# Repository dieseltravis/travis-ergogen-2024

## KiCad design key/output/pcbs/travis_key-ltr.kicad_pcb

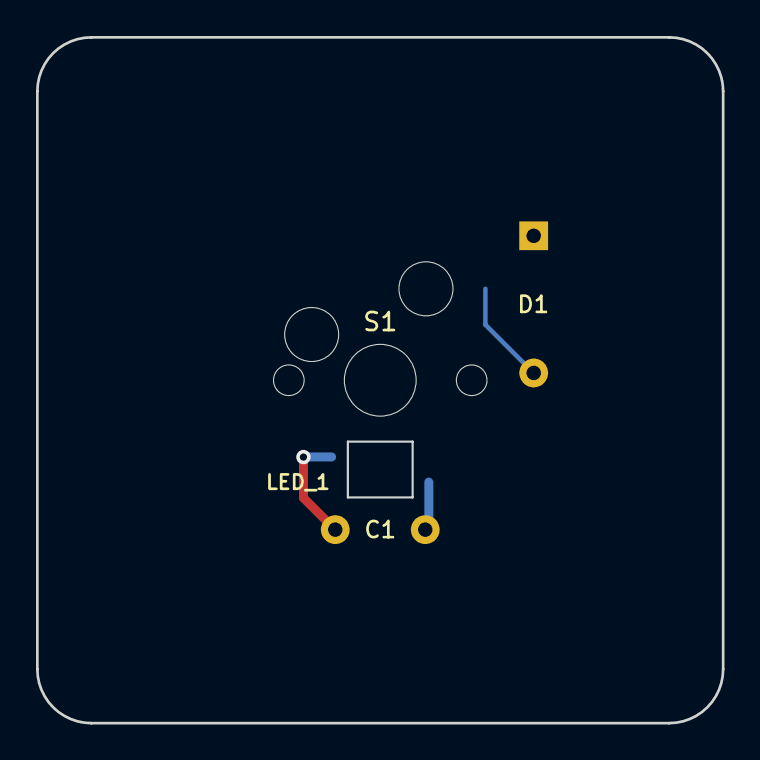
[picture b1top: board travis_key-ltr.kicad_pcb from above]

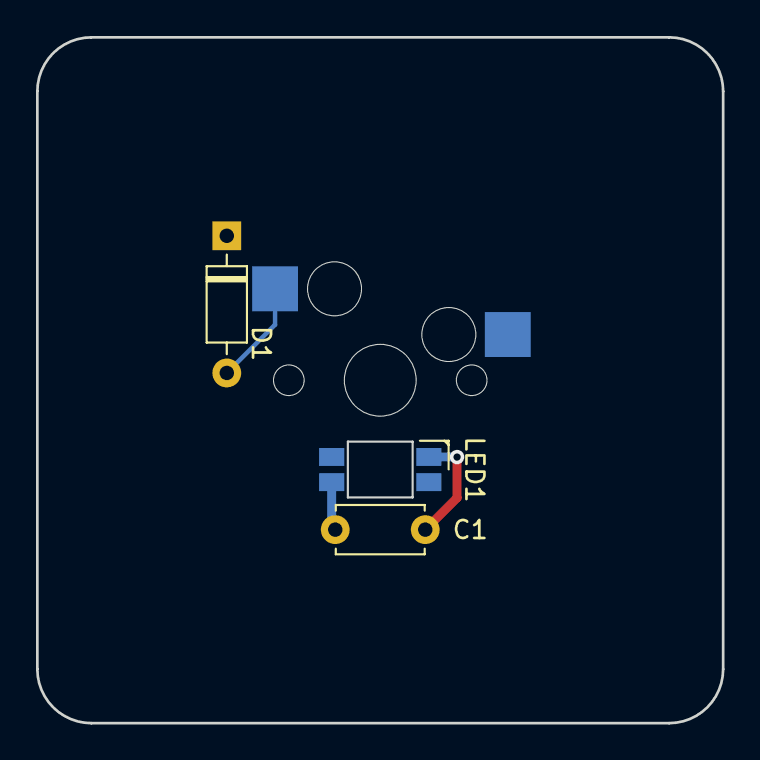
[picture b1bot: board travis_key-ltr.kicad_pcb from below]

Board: 2 copper layers, 38.1 x 38.1 mm, 4 parts (3 on the bottom side), 3 nets.

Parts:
C1: 104; C_Disc_D4.7mm_W2.5mm_P5.00mm
D1: 1N4148; Diode_DO-35
LED1: SK6812mini-e; led_SK6812mini-e (per-key single-side)
S1: MX

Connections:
GND: C1.2, LED1.3
RAW: C1.1, LED1.1
single_A_one: D1.2, S1.2

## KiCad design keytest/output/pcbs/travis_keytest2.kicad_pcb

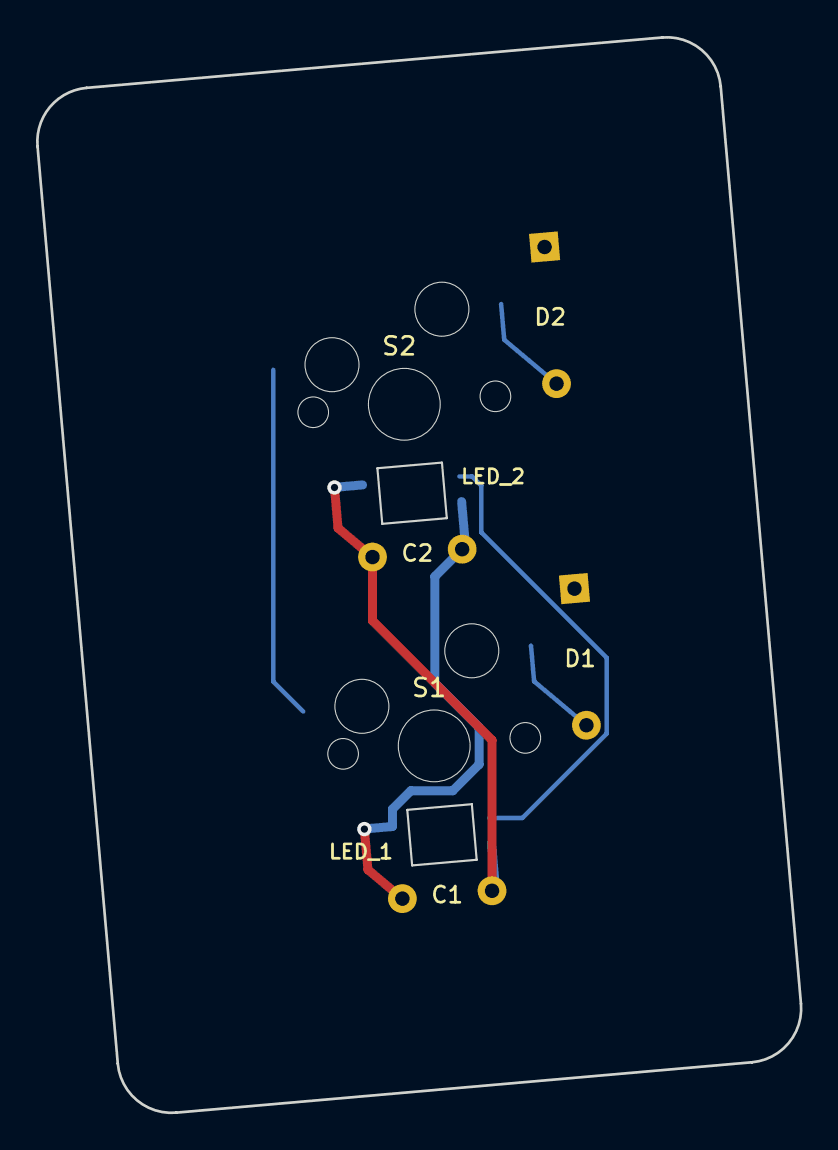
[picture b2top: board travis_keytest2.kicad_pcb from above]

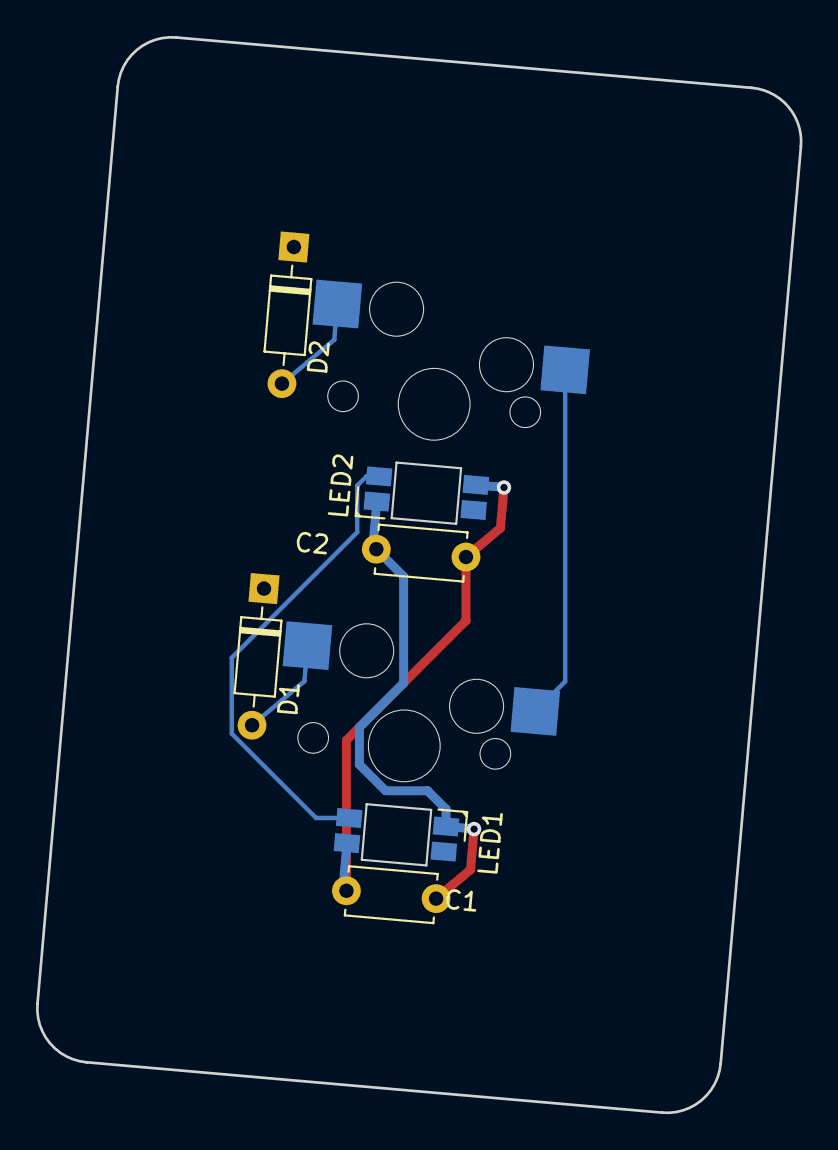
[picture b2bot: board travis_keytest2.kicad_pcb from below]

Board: 2 copper layers, 42.4 x 59.7 mm, 8 parts (6 on the bottom side), 6 nets.

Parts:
C1, C2: 104; C_Disc_D4.7mm_W2.5mm_P5.00mm
D1, D2: 1N4148; Diode_DO-35
LED1, LED2: SK6812mini-e; led_SK6812mini-e (per-key single-side)
S1, S2: Kailh MX Switch Sockets; MX

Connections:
GND: C1.2, C2.2, LED1.3, LED2.3
LED_2: LED1.2, LED2.4
RAW: C1.1, C2.1, LED1.1, LED2.1
col0: S1.1, S2.1
single_A_one: D1.2, S1.2
single_A_two: D2.2, S2.2

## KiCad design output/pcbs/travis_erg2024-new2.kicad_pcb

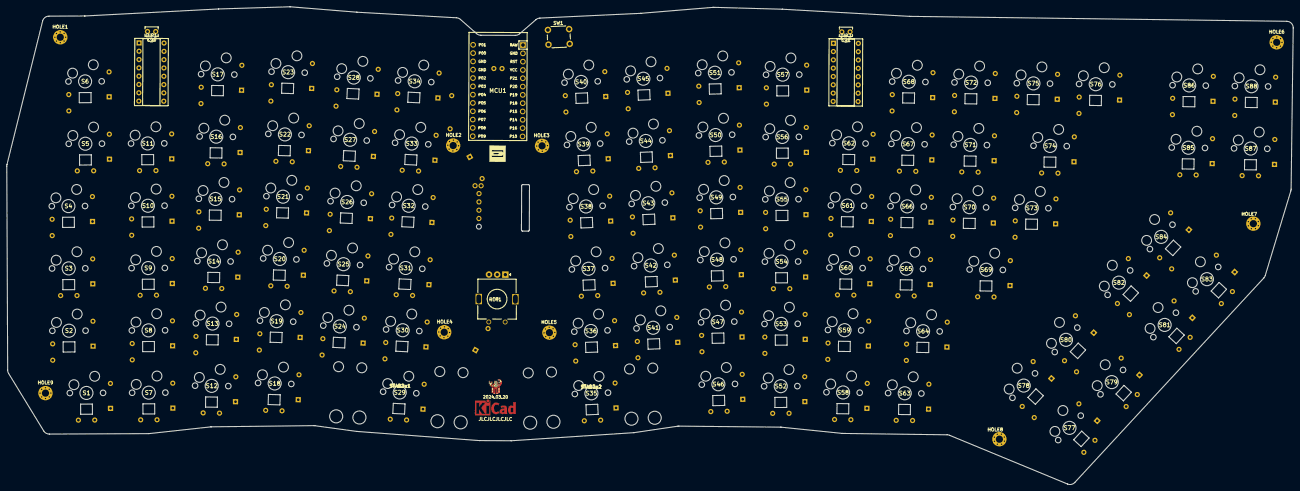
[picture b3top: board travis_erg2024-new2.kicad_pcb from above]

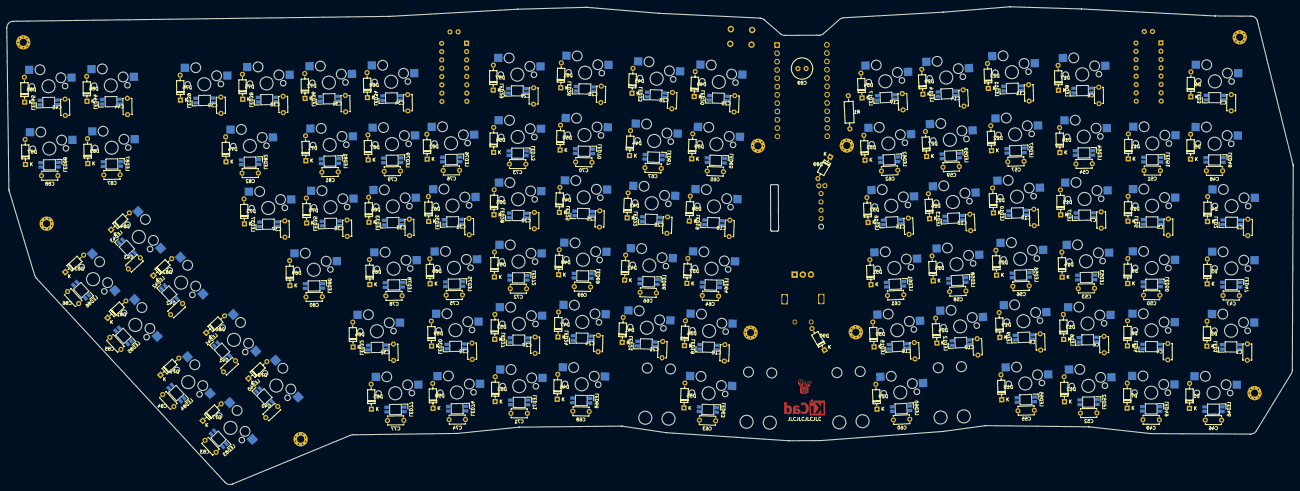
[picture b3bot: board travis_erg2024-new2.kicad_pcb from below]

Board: 2 copper layers, 393.3 x 146.1 mm, 379 parts (268 on the bottom side), 210 nets, no tracks yet.

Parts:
C1, C2, C3, C4, C5, C6, C7, C8, C9, C10, C11, C12, C13, C14, C15, C16, C17, C18, C19, C20, C21, C22, C23, C24, C25, C26, C27, C28, C29, C30, C31, C32, C33, C34, C35, C36, C37, C38, C39, C40, C41, C42, C43, C44, C45, C46, C47, C48, C49, C50, C51, C52, C53, C54, C55, C56, C57, C58, C59, C60, C61, C62, C63, C64, C65, C66, C67, C68, C69, C70, C71, C72, C73, C74, C75, C76, C77, C78, C79, C80, C81, C82, C83, C84, C85, C86, C87, C88: C_Disc_D4.7mm_W2.5mm_P5.00mm
C89: C_Radial_D6.3mm_H11.0mm_P2.50mm
C90, C91: C_Disc_D3.8mm_W2.6mm_P2.50mm
D1, D2, D3, D4, D5, D6, D7, D8, D9, D10, D11, D12, D13, D14, D15, D16, D17, D18, D19, D20, D21, D22, D23, D24, D25, D26, D27, D28, D29, D30, D31, D32, D33, D34, D35, D36, D37, D38, D39, D40, D41, D42, D43, D44, D45, D46, D47, D48, D49, D50, D51, D52, D53, D54, D55, D56, D57, D58, D59, D60, D61, D62, D63, D64, D65, D66, D67, D68, D69, D70, D71, D72, D73, D74, D75, D76, D77, D78, D79, D80, D81, D82, D83, D84, D85, D86, D87, D88, D89, D90: 1N4148; Diode_DO-35
DIP1, DIP2: DIP-16_W7.62mm_Socket
HOLE1, HOLE2, HOLE3, HOLE4, HOLE5, HOLE6, HOLE7, HOLE8, HOLE9: MountingHole_2.2mm_M2_Pad_Via
LED1, LED2, LED3, LED4, LED5, LED6, LED7, LED8, LED9, LED10, LED11, LED12, LED13, LED14, LED15, LED16, LED17, LED18, LED19, LED20, LED21, LED22, LED23, LED24, LED25, LED26, LED27, LED28, LED29, LED30, LED31, LED32, LED33, LED34, LED35, LED36, LED37, LED38, LED39, LED40, LED41, LED42, LED43, LED44, LED45, LED46, LED47, LED48, LED49, LED50, LED51, LED52, LED53, LED54, LED55, LED56, LED57, LED58, LED59, LED60, LED61, LED62, LED63, LED64, LED65, LED66, LED67, LED68, LED69, LED70, LED71, LED72, LED73, LED74, LED75, LED76, LED77, LED78, LED79, LED80, LED81, LED82, LED83, LED84, LED85, LED86, LED87, LED88: led_SK6812mini-e (per-keysingle-side)
LOGO1: ergogen
LOGO2: travis
MCU1: ProMicro
R1: R_Axial_DIN0207_L6.3mm_D2.5mm_P10.16mm_Horizontal
ROT1: rotary_encoder
S1, S2, S3, S4, S5, S6, S7, S8, S9, S10, S11, S12, S13, S14, S15, S16, S17, S18, S19, S20, S21, S22, S23, S24, S25, S26, S27, S28, S29, S30, S31, S32, S33, S34, S35, S36, S37, S38, S39, S40, S41, S42, S43, S44, S45, S46, S47, S48, S49, S50, S51, S52, S53, S54, S55, S56, S57, S58, S59, S60, S61, S62, S63, S64, S65, S66, S67, S68, S69, S70, S71, S72, S73, S74, S75, S76, S77, S78, S79, S80, S81, S82, S83, S84, S85, S86, S87, S88: MX
STAB2u1, STAB2u2: Stabilizer_MX_2.00u
STAB3u1, STAB3u2: Stabilizer_MX_3.00u
SW1: SW_PUSH_6mm_H4.3mm
SYM1: KiCad-Logo_5mm_Copper

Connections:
GND: C1.2, C2.2, C3.2, C4.2, C5.2, C6.2, C7.2, C8.2, C9.2, C10.2, C11.2, C12.2, C13.2, C14.2, C15.2, C16.2, C17.2, C18.2, C19.2, C20.2, C21.2, C22.2, C23.2, C24.2, C25.2, C26.2, C27.2, C28.2, C29.2, C30.2, C31.2, C32.2, C33.2, C34.2, C35.2, C36.2, C37.2, C38.2, C39.2, C40.2, C41.2, C42.2, C43.2, C44.2, C45.2, C46.2, C47.2, C48.2, C49.2, C50.2, C51.2, C52.2, C53.2, C54.2, C55.2, C56.2, C57.2, C58.2, C59.2, C60.2, C61.2, C62.2, C63.2, C64.2, C65.2, C66.2, C67.2, C68.2, C69.2, C70.2, C71.2, C72.2, C73.2, C74.2, C75.2, C76.2, C77.2, C78.2, C79.2, C80.2, C81.2, C82.2, C83.2, C84.2, C85.2, C86.2, C87.2, C88.2, C89.2, C90.2, C91.2, DIP1.4, DIP1.8, DIP2.4, DIP2.5, DIP2.8, LED1.3, LED2.3, LED3.3, LED4.3, LED5.3, LED6.3, LED7.3, LED8.3, LED9.3, LED10.3, LED11.3, LED12.3, LED13.3, LED14.3, LED15.3, LED16.3, LED17.3, LED18.3, LED19.3, LED20.3, LED21.3, LED22.3, LED23.3, LED24.3, LED25.3, LED26.3, LED27.3, LED28.3, LED29.3, LED30.3, LED31.3, LED32.3, LED33.3, LED34.3, LED35.3, LED36.3, LED37.3, LED38.3, LED39.3, LED40.3, LED41.3, LED42.3, LED43.3, LED44.3, LED45.3, LED46.3, LED47.3, LED48.3, LED49.3, LED50.3, LED51.3, LED52.3, LED53.3, LED54.3, LED55.3, LED56.3, LED57.3, LED58.3, LED59.3, LED60.3, LED61.3, LED62.3, LED63.3, LED64.3, LED65.3, LED66.3, LED67.3, LED68.3, LED69.3, LED70.3, LED71.3, LED72.3, LED73.3, LED74.3, LED75.3, LED76.3, LED77.3, LED78.3, LED79.3, LED80.3, LED81.3, LED82.3, LED83.3, LED84.3, LED85.3, LED86.3, LED87.3, LED88.3, MCU1.2, MCU1.15, MCU1.16, ROT1.B, SW1.1
LED: MCU1.24, R1.1
LED_0: LED17.4, R1.2
LED_1: LED14.4, LED17.2
LED_2: LED11.4, LED14.2
LED_3: LED8.4, LED11.2
LED_4: LED3.4, LED8.2
LED_5: LED3.2, LED48.4
LED_6: LED48.2, LED51.4
LED_7: LED51.2, LED54.4
LED_8: LED54.2, LED57.4
LED_9: LED57.2, LED59.4
LED_10: LED59.2, LED62.4
LED_11: LED16.4, LED62.2
LED_12: LED13.4, LED16.2
LED_13: LED10.4, LED13.2
LED_14: LED7.4, LED10.2
LED_15: LED5.4, LED7.2
LED_16: LED2.4, LED5.2
LED_17: LED2.2, LED47.4
LED_18: LED47.2, LED50.4
LED_19: LED50.2, LED53.4
LED_20: LED53.2, LED56.4
LED_21: LED56.2, LED58.4
LED_22: LED58.2, LED61.4
LED_23: LED15.4, LED61.2
LED_24: LED12.4, LED15.2
LED_25: LED9.4, LED12.2
LED_26: LED6.4, LED9.2
LED_27: LED4.4, LED6.2
LED_28: LED1.4, LED4.2
LED_29: LED1.2, LED46.4
LED_30: LED46.2, LED49.4
LED_31: LED49.2, LED52.4
LED_32: LED52.2, LED55.4
LED_33: LED55.2, LED60.4
LED_34: LED60.2, LED63.4
LED_35: LED63.2, LED68.4
LED_36: LED68.2, LED71.4
LED_37: LED71.2, LED74.4
LED_38: LED74.2, LED77.4
LED_39: LED40.4, LED77.2
LED_40: LED40.2, LED83.4
LED_41: LED83.2, LED84.4
LED_42: LED41.4, LED84.2
LED_43: LED32.4, LED41.2
LED_44: LED30.4, LED32.2
LED_45: LED27.4, LED30.2
LED_46: LED24.4, LED27.2
LED_47: LED21.4, LED24.2
LED_48: LED18.4, LED21.2
LED_49: LED18.2, LED64.4
LED_50: LED64.2, LED66.4
LED_51: LED66.2, LED69.4
LED_52: LED69.2, LED72.4
LED_53: LED72.2, LED75.4
LED_54: LED75.2, LED78.4
LED_55: LED78.2, LED80.4
LED_56: LED42.4, LED80.2
LED_57: LED42.2, LED85.4
LED_58: LED85.2, LED86.4
LED_59: LED43.4, LED86.2
LED_60: LED37.4, LED43.2
LED_61: LED35.4, LED37.2
LED_62: LED33.4, LED35.2
LED_63: LED31.4, LED33.2
LED_64: LED28.4, LED31.2
LED_65: LED25.4, LED28.2
LED_66: LED22.4, LED25.2
LED_67: LED19.4, LED22.2
LED_68: LED19.2, LED65.4
LED_69: LED65.2, LED67.4
LED_70: LED67.2, LED70.4
LED_71: LED70.2, LED73.4
LED_72: LED73.2, LED76.4
LED_73: LED76.2, LED79.4
LED_74: LED79.2, LED81.4
LED_75: LED81.2, LED82.4
LED_76: LED82.2, LED87.4
LED_77: LED87.2, LED88.4
LED_78: LED45.4, LED88.2
LED_79: LED44.4, LED45.2
LED_80: LED39.4, LED44.2
LED_81: LED38.4, LED39.2
LED_82: LED36.4, LED38.2
LED_83: LED34.4, LED36.2
LED_84: LED29.4, LED34.2
LED_85: LED26.4, LED29.2
LED_86: LED23.4, LED26.2
LED_87: LED20.4, LED23.2
RAW: C1.1, C2.1, C3.1, C4.1, C5.1, C6.1, C7.1, C8.1, C9.1, C10.1, C11.1, C12.1, C13.1, C14.1, C15.1, C16.1, C17.1, C18.1, C19.1, C20.1, C21.1, C22.1, C23.1, C24.1, C25.1, C26.1, C27.1, C28.1, C29.1, C30.1, C31.1, C32.1, C33.1, C34.1, C35.1, C36.1, C37.1, C38.1, C39.1, C40.1, C41.1, C42.1, C43.1, C44.1, C45.1, C46.1, C47.1, C48.1, C49.1, C50.1, C51.1, C52.1, C53.1, C54.1, C55.1, C56.1, C57.1, C58.1, C59.1, C60.1, C61.1, C62.1, C63.1, C64.1, C65.1, C66.1, C67.1, C68.1, C69.1, C70.1, C71.1, C72.1, C73.1, C74.1, C75.1, C76.1, C77.1, C78.1, C79.1, C80.1, C81.1, C82.1, C83.1, C84.1, C85.1, C86.1, C87.1, C88.1, C89.1, LED1.1, LED2.1, LED3.1, LED4.1, LED5.1, LED6.1, LED7.1, LED8.1, LED9.1, LED10.1, LED11.1, LED12.1, LED13.1, LED14.1, LED15.1, LED16.1, LED17.1, LED18.1, LED19.1, LED20.1, LED21.1, LED22.1, LED23.1, LED24.1, LED25.1, LED26.1, LED27.1, LED28.1, LED29.1, LED30.1, LED31.1, LED32.1, LED33.1, LED34.1, LED35.1, LED36.1, LED37.1, LED38.1, LED39.1, LED40.1, LED41.1, LED42.1, LED43.1, LED44.1, LED45.1, LED46.1, LED47.1, LED48.1, LED49.1, LED50.1, LED51.1, LED52.1, LED53.1, LED54.1, LED55.1, LED56.1, LED57.1, LED58.1, LED59.1, LED60.1, LED61.1, LED62.1, LED63.1, LED64.1, LED65.1, LED66.1, LED67.1, LED68.1, LED69.1, LED70.1, LED71.1, LED72.1, LED73.1, LED74.1, LED75.1, LED76.1, LED77.1, LED78.1, LED79.1, LED80.1, LED81.1, LED82.1, LED83.1, LED84.1, LED85.1, LED86.1, LED87.1, LED88.1, MCU1.1
RST: MCU1.3, SW1.2
VCC: C90.1, C91.1, DIP1.6, DIP1.16, DIP2.16, MCU1.4
arrows_left_bottom: D77.2, S77.2
arrows_left_top: D78.2, S78.2
arrows_right_bottom: D79.2, S79.2
arrows_right_top: D80.2, S80.2
col0: DIP1.14, S1.1, S2.1, S3.1, S4.1, S5.1, S6.1
col1: DIP1.15, S7.1, S8.1, S9.1, S10.1, S11.1
col2: MCU1.10, S12.1, S13.1, S14.1, S15.1, S16.1, S17.1
col3: MCU1.9, S18.1, S19.1, S20.1, S21.1, S22.1, S23.1
col4: MCU1.8, ROT1.1, S24.1, S25.1, S26.1, S27.1, S28.1
col5: MCU1.7, S29.1, S30.1, S31.1, S32.1, S33.1, S34.1
col6: MCU1.6, S35.1, S36.1, S37.1, S38.1, S39.1, S40.1
col7: MCU1.5, S41.1, S42.1, S43.1, S44.1, S45.1
col8: DIP2.15, S46.1, S47.1, S48.1, S49.1, S50.1, S51.1
col9: DIP2.14, S52.1, S53.1, S54.1, S55.1, S56.1, S57.1
col10: DIP2.13, S58.1, S59.1, S60.1, S61.1, S62.1
col11: DIP2.12, S63.1, S64.1, S65.1, S66.1, S67.1, S68.1
col12: DIP2.11, S69.1, S70.1, S71.1, S72.1
col13: DIP2.10, S73.1, S74.1, S75.1, S76.1
col14: DIP2.9, S78.1, S80.1, S82.1, S84.1, S85.1, S86.1
col15: DIP2.7, S77.1, S79.1, S81.1, S83.1, S87.1, S88.1
encA: MCU1.11, ROT1.A
encC: MCU1.12, ROT1.C
enc_to: D90.2, ROT1.2
matrixl_index_bottom: D24.2, S24.2
matrixl_index_func: D28.2, S28.2
matrixl_index_home: D25.2, S25.2
matrixl_index_num: D27.2, S27.2
matrixl_index_top: D26.2, S26.2
matrixl_inner_bottom: D30.2, S30.2
matrixl_inner_func: D34.2, S34.2
matrixl_inner_home: D31.2, S31.2
matrixl_inner_mod: D29.2, S29.2
matrixl_inner_num: D33.2, S33.2
matrixl_inner_top: D32.2, S32.2
matrixl_middle_bottom: D19.2, S19.2
matrixl_middle_func: D23.2, S23.2
matrixl_middle_home: D20.2, S20.2
matrixl_middle_mod: D18.2, S18.2
matrixl_middle_num: D22.2, S22.2
matrixl_middle_top: D21.2, S21.2
matrixl_outer_bottom: D2.2, S2.2
matrixl_outer_func: D6.2, S6.2
matrixl_outer_home: D3.2, S3.2
matrixl_outer_mod: D1.2, S1.2
matrixl_outer_num: D5.2, S5.2
matrixl_outer_top: D4.2, S4.2
matrixl_pinky_bottom: D8.2, S8.2
matrixl_pinky_home: D9.2, S9.2
matrixl_pinky_mod: D7.2, S7.2
matrixl_pinky_num: D11.2, S11.2
matrixl_pinky_top: D10.2, S10.2
matrixl_ring_bottom: D13.2, S13.2
matrixl_ring_func: D17.2, S17.2
matrixl_ring_home: D14.2, S14.2
matrixl_ring_mod: D12.2, S12.2
matrixl_ring_num: D16.2, S16.2
matrixl_ring_top: D15.2, S15.2
matrixr_index_bottom: D41.2, S41.2
matrixr_index_func: D45.2, S45.2
matrixr_index_home: D42.2, S42.2
matrixr_index_num: D44.2, S44.2
matrixr_index_top: D43.2, S43.2
matrixr_inner_bottom: D36.2, S36.2
matrixr_inner_func: D40.2, S40.2
matrixr_inner_home: D37.2, S37.2
matrixr_inner_mod: D35.2, S35.2
matrixr_inner_num: D39.2, S39.2
matrixr_inner_top: D38.2, S38.2
matrixr_middle_bottom: D47.2, S47.2
matrixr_middle_func: D51.2, S51.2
matrixr_middle_home: D48.2, S48.2
matrixr_middle_mod: D46.2, S46.2
matrixr_middle_num: D50.2, S50.2
matrixr_middle_top: D49.2, S49.2
matrixr_outer2_func: D72.2, S72.2
matrixr_outer2_home: D69.2, S69.2
matrixr_outer2_num: D71.2, S71.2
matrixr_outer2_top: D70.2, S70.2
matrixr_outer3_func: D75.2, S75.2
matrixr_outer3_num: D74.2, S74.2
matrixr_outer3_top: D73.2, S73.2
matrixr_outer4_func: D76.2, S76.2
matrixr_outer_bottom: D64.2, S64.2
matrixr_outer_func: D68.2, S68.2
matrixr_outer_home: D65.2, S65.2
matrixr_outer_mod: D63.2, S63.2
matrixr_outer_num: D67.2, S67.2
matrixr_outer_top: D66.2, S66.2
matrixr_pinky_bottom: D59.2, S59.2
matrixr_pinky_home: D60.2, S60.2
matrixr_pinky_mod: D58.2, S58.2
matrixr_pinky_num: D62.2, S62.2
matrixr_pinky_top: D61.2, S61.2
matrixr_ring_bottom: D53.2, S53.2
matrixr_ring_func: D57.2, S57.2
matrixr_ring_home: D54.2, S54.2
matrixr_ring_mod: D52.2, S52.2
matrixr_ring_num: D56.2, S56.2
matrixr_ring_top: D55.2, S55.2
mux0: DIP1.1, DIP2.1, MCU1.17
mux1: DIP1.2, DIP2.2, MCU1.18
mux2: DIP1.3, DIP2.3, MCU1.19
mux3: DIP1.5, DIP2.6, MCU1.20
pages_left_bottom: D81.2, S81.2
pages_left_top: D82.2, S82.2
pages_right_bottom: D83.2, S83.2
pages_right_top: D84.2, S84.2
row0: D6.1, D17.1, D23.1, D28.1, D34.1, D40.1, D45.1, D51.1, D57.1, D68.1, D72.1, D75.1, D86.1, D88.1, D89.1, DIP1.13
row1: D5.1, D11.1, D16.1, D22.1, D27.1, D33.1, D39.1, D44.1, D50.1, D56.1, D62.1, D67.1, D71.1, D74.1, D85.1, D87.1, DIP1.12
row2: D4.1, D10.1, D15.1, D21.1, D26.1, D32.1, D38.1, D43.1, D49.1, D55.1, D61.1, D66.1, D70.1, D73.1, D83.1, D84.1, DIP1.11
row3: D3.1, D9.1, D14.1, D20.1, D25.1, D31.1, D37.1, D42.1, D48.1, D54.1, D60.1, D65.1, D69.1, D76.1, D81.1, D82.1, DIP1.10
row4: D2.1, D8.1, D13.1, D19.1, D24.1, D30.1, D36.1, D41.1, D47.1, D53.1, D59.1, D64.1, D79.1, D80.1, DIP1.9
row5: D1.1, D7.1, D12.1, D18.1, D29.1, D35.1, D46.1, D52.1, D58.1, D63.1, D77.1, D78.1, D90.1, DIP1.7
special_left_bottom: D85.2, S85.2
special_left_top: D86.2, S86.2
special_right_bottom: D87.2, S87.2
special_right_top: D88.2, S88.2

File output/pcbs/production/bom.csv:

Designator,Footprint,Quantity,Value,LCSC Part #
C1,C_Radial_D6.3mm_H11.0mm_P2.50mm,1,C_Radial_D6.3mm_H11.0mm_P2.50mm,
"C2, C3",C_Disc_D3.8mm_W2.6mm_P2.50mm,2,C_Disc_D3.8mm_W2.6mm_P2.50mm,
"D1, D2, KD1, KD10, KD11, KD12, KD13, KD14, KD15, KD16, KD17, KD18, KD19, KD2, KD20, KD21, KD22, KD23, KD24, KD25, KD26, KD27, KD28, KD29, KD3, KD30, KD31, KD32, KD33, KD34, KD35, KD36, KD37, KD38, KD39, KD4, KD40, KD41, KD42, KD43, KD44, KD45, KD46, KD47, KD48, KD49, KD5, KD50, KD51, KD52, KD53, KD54, KD55, KD56, KD57, KD58, KD59, KD6, KD60, KD61, KD62, KD63, KD64, KD65, KD66, KD67, KD68, KD69, KD7, KD70, KD71, KD72, KD73, KD74, KD75, KD76, KD77, KD78, KD79, KD8, KD80, KD81, KD82, KD83, KD84, KD85, KD86, KD87, KD88, KD9",Diode_DO-35,90,1N4148,
"DIP1, DIP2",DIP-16_W7.62mm_Socket,2,DIP-16_W7.62mm_Socket,
"HOLE1, HOLE2, HOLE3, HOLE4, HOLE5, HOLE6, HOLE7, HOLE8, HOLE9",MountingHole_2.2mm_M2_Pad_Via,9,,
"KC1, KC10, KC11, KC12, KC13, KC14, KC15, KC16, KC17, KC18, KC19, KC2, KC20, KC21, KC22, KC23, KC24, KC25, KC26, KC27, KC28, KC29, KC3, KC30, KC31, KC32, KC33, KC34, KC35, KC36, KC37, KC38, KC39, KC4, KC40, KC41, KC42, KC43, KC44, KC45, KC46, KC47, KC48, KC49, KC5, KC50, KC51, KC52, KC53, KC54, KC55, KC56, KC57, KC58, KC59, KC6, KC60, KC61, KC62, KC63, KC64, KC65, KC66, KC67, KC68, KC69, KC7, KC70, KC71, KC72, KC73, KC74, KC75, KC76, KC77, KC78, KC79, KC8, KC80, KC81, KC82, KC83, KC84, KC85, KC86, KC87, KC88, KC9",C_Disc_D4.7mm_W2.5mm_P5.00mm,88,104,
"KLED1, KLED10, KLED11, KLED12, KLED13, KLED14, KLED15, KLED16, KLED17, KLED18, KLED19, KLED2, KLED20, KLED21, KLED22, KLED23, KLED24, KLED25, KLED26, KLED27, KLED28, KLED29, KLED3, KLED30, KLED31, KLED32, KLED33, KLED34, KLED35, KLED36, KLED37, KLED38, KLED39, KLED4, KLED40, KLED41, KLED42, KLED43, KLED44, KLED45, KLED46, KLED47, KLED48, KLED49, KLED5, KLED50, KLED51, KLED52, KLED53, KLED54, KLED55, KLED56, KLED57, KLED58, KLED59, KLED6, KLED60, KLED61, KLED62, KLED63, KLED64, KLED65, KLED66, KLED67, KLED68, KLED69, KLED7, KLED70, KLED71, KLED72, KLED73, KLED74, KLED75, KLED76, KLED77, KLED78, KLED79, KLED8, KLED80, KLED81, KLED82, KLED83, KLED84, KLED85, KLED86, KLED87, KLED88, KLED9",led_SK6812mini-e (per-key single-side),88,SK6812mini-e,
"KSW1, KSW10, KSW11, KSW12, KSW13, KSW14, KSW15, KSW16, KSW17, KSW18, KSW19, KSW2, KSW20, KSW21, KSW22, KSW23, KSW24, KSW25, KSW26, KSW27, KSW28, KSW29, KSW3, KSW30, KSW31, KSW32, KSW33, KSW34, KSW35, KSW36, KSW37, KSW38, KSW39, KSW4, KSW40, KSW41, KSW42, KSW43, KSW44, KSW45, KSW46, KSW47, KSW48, KSW49, KSW5, KSW50, KSW51, KSW52, KSW53, KSW54, KSW55, KSW56, KSW57, KSW58, KSW59, KSW6, KSW60, KSW61, KSW62, KSW63, KSW64, KSW65, KSW66, KSW67, KSW68, KSW69, KSW7, KSW70, KSW71, KSW72, KSW73, KSW74, KSW75, KSW76, KSW77, KSW78, KSW79, KSW8, KSW80, KSW81, KSW82, KSW83, KSW84, KSW85, KSW86, KSW87, KSW88, KSW9",MX,88,Kailh MX Switch Sockets,
MCU1,ProMicro,1,,
R1,R_Axial_DIN0207_L6.3mm_D2.5mm_P10.16mm_Horizontal,1,R_Axial_DIN0207_L6.3mm_D2.5mm_P10.16mm_Horizontal,
ROT1,rotary_encoder,1,,
SW1,SW_PUSH_6mm_H4.3mm,1,SW_PUSH_6mm_H4.3mm,

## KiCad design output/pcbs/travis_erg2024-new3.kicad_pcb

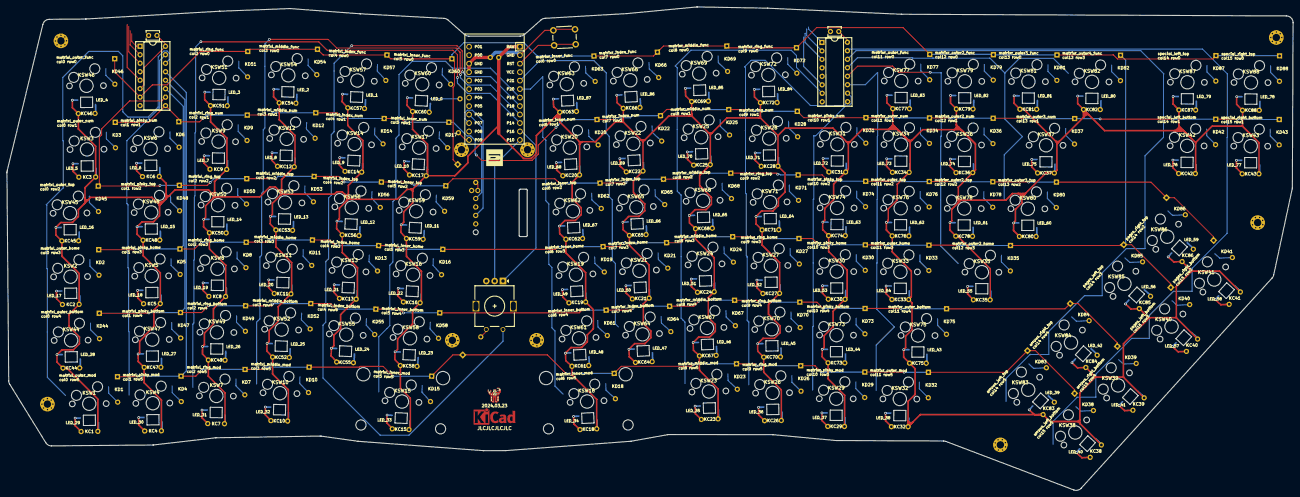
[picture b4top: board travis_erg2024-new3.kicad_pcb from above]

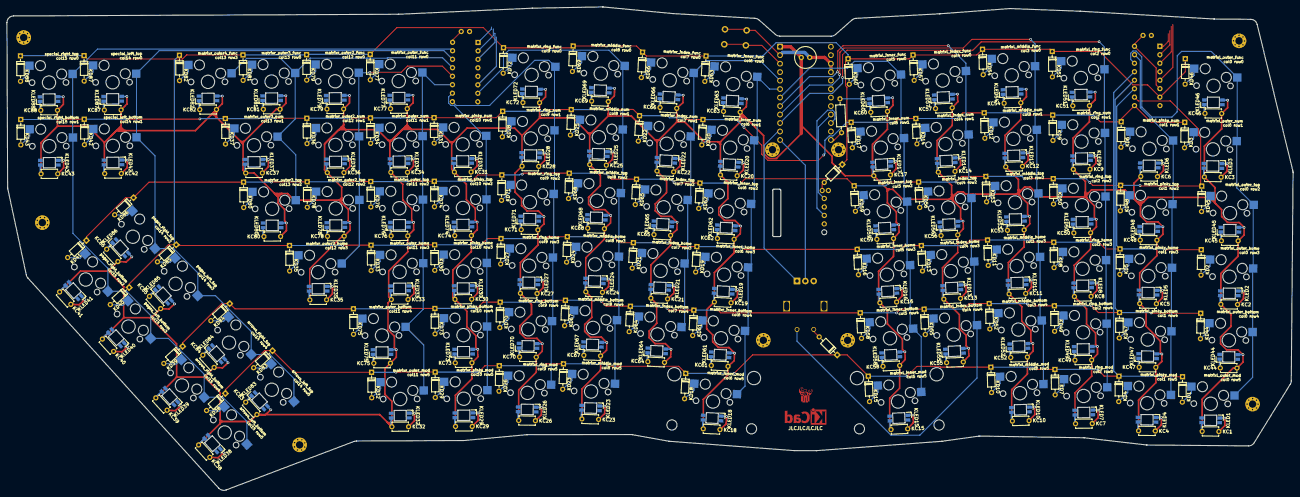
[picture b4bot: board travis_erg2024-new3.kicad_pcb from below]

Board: 2 copper layers, 385.3 x 144.8 mm, 377 parts (268 on the bottom side), 210 nets.

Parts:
C1: C_Radial_D6.3mm_H11.0mm_P2.50mm
C2, C3: C_Disc_D3.8mm_W2.6mm_P2.50mm
D1, D2: 1N4148; Diode_DO-35
DIP1, DIP2: DIP-16_W7.62mm_Socket
HOLE1, HOLE2, HOLE3, HOLE4, HOLE5, HOLE6, HOLE7, HOLE8, HOLE9: MountingHole_2.2mm_M2_Pad_Via
KC1, KC2, KC3, KC4, KC5, KC6, KC7, KC8, KC9, KC10, KC11, KC12, KC13, KC14, KC15, KC16, KC17, KC18, KC19, KC20, KC21, KC22, KC23, KC24, KC25, KC26, KC27, KC28, KC29, KC30, KC31, KC32, KC33, KC34, KC35, KC36, KC37, KC38, KC39, KC40, KC41, KC42, KC43, KC44, KC45, KC46, KC47, KC48, KC49, KC50, KC51, KC52, KC53, KC54, KC55, KC56, KC57, KC58, KC59, KC60, KC61, KC62, KC63, KC64, KC65, KC66, KC67, KC68, KC69, KC70, KC71, KC72, KC73, KC74, KC75, KC76, KC77, KC78, KC79, KC80, KC81, KC82, KC83, KC84, KC85, KC86, KC87, KC88: 104; C_Disc_D4.7mm_W2.5mm_P5.00mm
KD1, KD2, KD3, KD4, KD5, KD6, KD7, KD8, KD9, KD10, KD11, KD12, KD13, KD14, KD15, KD16, KD17, KD18, KD19, KD20, KD21, KD22, KD23, KD24, KD25, KD26, KD27, KD28, KD29, KD30, KD31, KD32, KD33, KD34, KD35, KD36, KD37, KD38, KD39, KD40, KD41, KD42, KD43, KD44, KD45, KD46, KD47, KD48, KD49, KD50, KD51, KD52, KD53, KD54, KD55, KD56, KD57, KD58, KD59, KD60, KD61, KD62, KD63, KD64, KD65, KD66, KD67, KD68, KD69, KD70, KD71, KD72, KD73, KD74, KD75, KD76, KD77, KD78, KD79, KD80, KD81, KD82, KD83, KD84, KD85, KD86, KD87, KD88: 1N4148; Diode_DO-35
KLED1, KLED2, KLED3, KLED4, KLED5, KLED6, KLED7, KLED8, KLED9, KLED10, KLED11, KLED12, KLED13, KLED14, KLED15, KLED16, KLED17, KLED18, KLED19, KLED20, KLED21, KLED22, KLED23, KLED24, KLED25, KLED26, KLED27, KLED28, KLED29, KLED30, KLED31, KLED32, KLED33, KLED34, KLED35, KLED36, KLED37, KLED38, KLED39, KLED40, KLED41, KLED42, KLED43, KLED44, KLED45, KLED46, KLED47, KLED48, KLED49, KLED50, KLED51, KLED52, KLED53, KLED54, KLED55, KLED56, KLED57, KLED58, KLED59, KLED60, KLED61, KLED62, KLED63, KLED64, KLED65, KLED66, KLED67, KLED68, KLED69, KLED70, KLED71, KLED72, KLED73, KLED74, KLED75, KLED76, KLED77, KLED78, KLED79, KLED80, KLED81, KLED82, KLED83, KLED84, KLED85, KLED86, KLED87, KLED88: SK6812mini-e; led_SK6812mini-e (per-key single-side)
KSW1, KSW2, KSW3, KSW4, KSW5, KSW6, KSW7, KSW8, KSW9, KSW10, KSW11, KSW12, KSW13, KSW14, KSW15, KSW16, KSW17, KSW18, KSW19, KSW20, KSW21, KSW22, KSW23, KSW24, KSW25, KSW26, KSW27, KSW28, KSW29, KSW30, KSW31, KSW32, KSW33, KSW34, KSW35, KSW36, KSW37, KSW38, KSW39, KSW40, KSW41, KSW42, KSW43, KSW44, KSW45, KSW46, KSW47, KSW48, KSW49, KSW50, KSW51, KSW52, KSW53, KSW54, KSW55, KSW56, KSW57, KSW58, KSW59, KSW60, KSW61, KSW62, KSW63, KSW64, KSW65, KSW66, KSW67, KSW68, KSW69, KSW70, KSW71, KSW72, KSW73, KSW74, KSW75, KSW76, KSW77, KSW78, KSW79, KSW80, KSW81, KSW82, KSW83, KSW84, KSW85, KSW86, KSW87, KSW88: Kailh MX Switch Sockets; MX
LOGO1: ergogen
LOGO2: travis
MCU1: ProMicro
R1: R_Axial_DIN0207_L6.3mm_D2.5mm_P10.16mm_Horizontal
ROT1: rotary_encoder
STAB2u1, STAB2u2: Stabilizer_MX_2.00u
SW1: SW_PUSH_6mm_H4.3mm
SYM1: KiCad-Logo_5mm_Copper

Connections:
GND: C1.2, C2.2, C3.2, DIP1.4, DIP1.8, DIP2.4, DIP2.5, DIP2.8, KC1.2, KC2.2, KC3.2, KC4.2, KC5.2, KC6.2, KC7.2, KC8.2, KC9.2, KC10.2, KC11.2, KC12.2, KC13.2, KC14.2, KC15.2, KC16.2, KC17.2, KC18.2, KC19.2, KC20.2, KC21.2, KC22.2, KC23.2, KC24.2, KC25.2, KC26.2, KC27.2, KC28.2, KC29.2, KC30.2, KC31.2, KC32.2, KC33.2, KC34.2, KC35.2, KC36.2, KC37.2, KC38.2, KC39.2, KC40.2, KC41.2, KC42.2, KC43.2, KC44.2, KC45.2, KC46.2, KC47.2, KC48.2, KC49.2, KC50.2, KC51.2, KC52.2, KC53.2, KC54.2, KC55.2, KC56.2, KC57.2, KC58.2, KC59.2, KC60.2, KC61.2, KC62.2, KC63.2, KC64.2, KC65.2, KC66.2, KC67.2, KC68.2, KC69.2, KC70.2, KC71.2, KC72.2, KC73.2, KC74.2, KC75.2, KC76.2, KC77.2, KC78.2, KC79.2, KC80.2, KC81.2, KC82.2, KC83.2, KC84.2, KC85.2, KC86.2, KC87.2, KC88.2, KLED1.3, KLED2.3, KLED3.3, KLED4.3, KLED5.3, KLED6.3, KLED7.3, KLED8.3, KLED9.3, KLED10.3, KLED11.3, KLED12.3, KLED13.3, KLED14.3, KLED15.3, KLED16.3, KLED17.3, KLED18.3, KLED19.3, KLED20.3, KLED21.3, KLED22.3, KLED23.3, KLED24.3, KLED25.3, KLED26.3, KLED27.3, KLED28.3, KLED29.3, KLED30.3, KLED31.3, KLED32.3, KLED33.3, KLED34.3, KLED35.3, KLED36.3, KLED37.3, KLED38.3, KLED39.3, KLED40.3, KLED41.3, KLED42.3, KLED43.3, KLED44.3, KLED45.3, KLED46.3, KLED47.3, KLED48.3, KLED49.3, KLED50.3, KLED51.3, KLED52.3, KLED53.3, KLED54.3, KLED55.3, KLED56.3, KLED57.3, KLED58.3, KLED59.3, KLED60.3, KLED61.3, KLED62.3, KLED63.3, KLED64.3, KLED65.3, KLED66.3, KLED67.3, KLED68.3, KLED69.3, KLED70.3, KLED71.3, KLED72.3, KLED73.3, KLED74.3, KLED75.3, KLED76.3, KLED77.3, KLED78.3, KLED79.3, KLED80.3, KLED81.3, KLED82.3, KLED83.3, KLED84.3, KLED85.3, KLED86.3, KLED87.3, KLED88.3, MCU1.2, MCU1.15, MCU1.16, ROT1.B, SW1.1
LED: MCU1.24, R1.1
LED_0: KLED60.4, R1.2
LED_1: KLED57.4, KLED60.2
LED_2: KLED54.4, KLED57.2
LED_3: KLED51.4, KLED54.2
LED_4: KLED46.4, KLED51.2
LED_5: KLED3.4, KLED46.2
LED_6: KLED3.2, KLED6.4
LED_7: KLED6.2, KLED9.4
LED_8: KLED9.2, KLED12.4
LED_9: KLED12.2, KLED14.4
LED_10: KLED14.2, KLED17.4
LED_11: KLED17.2, KLED59.4
LED_12: KLED56.4, KLED59.2
LED_13: KLED53.4, KLED56.2
LED_14: KLED50.4, KLED53.2
LED_15: KLED48.4, KLED50.2
LED_16: KLED45.4, KLED48.2
LED_17: KLED2.4, KLED45.2
LED_18: KLED2.2, KLED5.4
LED_19: KLED5.2, KLED8.4
LED_20: KLED8.2, KLED11.4
LED_21: KLED11.2, KLED13.4
LED_22: KLED13.2, KLED16.4
LED_23: KLED16.2, KLED58.4
LED_24: KLED55.4, KLED58.2
LED_25: KLED52.4, KLED55.2
LED_26: KLED49.4, KLED52.2
LED_27: KLED47.4, KLED49.2
LED_28: KLED44.4, KLED47.2
LED_29: KLED1.4, KLED44.2
LED_30: KLED1.2, KLED4.4
LED_31: KLED4.2, KLED7.4
LED_32: KLED7.2, KLED10.4
LED_33: KLED10.2, KLED15.4
LED_34: KLED15.2, KLED18.4
LED_35: KLED18.2, KLED23.4
LED_36: KLED23.2, KLED26.4
LED_37: KLED26.2, KLED29.4
LED_38: KLED29.2, KLED32.4
LED_39: KLED32.2, KLED83.4
LED_40: KLED38.4, KLED83.2
LED_41: KLED38.2, KLED39.4
LED_42: KLED39.2, KLED84.4
LED_43: KLED75.4, KLED84.2
LED_44: KLED73.4, KLED75.2
LED_45: KLED70.4, KLED73.2
LED_46: KLED67.4, KLED70.2
LED_47: KLED64.4, KLED67.2
LED_48: KLED61.4, KLED64.2
LED_49: KLED19.4, KLED61.2
LED_50: KLED19.2, KLED21.4
LED_51: KLED21.2, KLED24.4
LED_52: KLED24.2, KLED27.4
LED_53: KLED27.2, KLED30.4
LED_54: KLED30.2, KLED33.4
LED_55: KLED33.2, KLED35.4
LED_56: KLED35.2, KLED85.4
LED_57: KLED40.4, KLED85.2
LED_58: KLED40.2, KLED41.4
LED_59: KLED41.2, KLED86.4
LED_60: KLED80.4, KLED86.2
LED_61: KLED78.4, KLED80.2
LED_62: KLED76.4, KLED78.2
LED_63: KLED74.4, KLED76.2
LED_64: KLED71.4, KLED74.2
LED_65: KLED68.4, KLED71.2
LED_66: KLED65.4, KLED68.2
LED_67: KLED62.4, KLED65.2
LED_68: KLED20.4, KLED62.2
LED_69: KLED20.2, KLED22.4
LED_70: KLED22.2, KLED25.4
LED_71: KLED25.2, KLED28.4
LED_72: KLED28.2, KLED31.4
LED_73: KLED31.2, KLED34.4
LED_74: KLED34.2, KLED36.4
LED_75: KLED36.2, KLED37.4
LED_76: KLED37.2, KLED42.4
LED_77: KLED42.2, KLED43.4
LED_78: KLED43.2, KLED88.4
LED_79: KLED87.4, KLED88.2
LED_80: KLED82.4, KLED87.2
LED_81: KLED81.4, KLED82.2
LED_82: KLED79.4, KLED81.2
LED_83: KLED77.4, KLED79.2
LED_84: KLED72.4, KLED77.2
LED_85: KLED69.4, KLED72.2
LED_86: KLED66.4, KLED69.2
LED_87: KLED63.4, KLED66.2
RAW: C1.1, KC1.1, KC2.1, KC3.1, KC4.1, KC5.1, KC6.1, KC7.1, KC8.1, KC9.1, KC10.1, KC11.1, KC12.1, KC13.1, KC14.1, KC15.1, KC16.1, KC17.1, KC18.1, KC19.1, KC20.1, KC21.1, KC22.1, KC23.1, KC24.1, KC25.1, KC26.1, KC27.1, KC28.1, KC29.1, KC30.1, KC31.1, KC32.1, KC33.1, KC34.1, KC35.1, KC36.1, KC37.1, KC38.1, KC39.1, KC40.1, KC41.1, KC42.1, KC43.1, KC44.1, KC45.1, KC46.1, KC47.1, KC48.1, KC49.1, KC50.1, KC51.1, KC52.1, KC53.1, KC54.1, KC55.1, KC56.1, KC57.1, KC58.1, KC59.1, KC60.1, KC61.1, KC62.1, KC63.1, KC64.1, KC65.1, KC66.1, KC67.1, KC68.1, KC69.1, KC70.1, KC71.1, KC72.1, KC73.1, KC74.1, KC75.1, KC76.1, KC77.1, KC78.1, KC79.1, KC80.1, KC81.1, KC82.1, KC83.1, KC84.1, KC85.1, KC86.1, KC87.1, KC88.1, KLED1.1, KLED2.1, KLED3.1, KLED4.1, KLED5.1, KLED6.1, KLED7.1, KLED8.1, KLED9.1, KLED10.1, KLED11.1, KLED12.1, KLED13.1, KLED14.1, KLED15.1, KLED16.1, KLED17.1, KLED18.1, KLED19.1, KLED20.1, KLED21.1, KLED22.1, KLED23.1, KLED24.1, KLED25.1, KLED26.1, KLED27.1, KLED28.1, KLED29.1, KLED30.1, KLED31.1, KLED32.1, KLED33.1, KLED34.1, KLED35.1, KLED36.1, KLED37.1, KLED38.1, KLED39.1, KLED40.1, KLED41.1, KLED42.1, KLED43.1, KLED44.1, KLED45.1, KLED46.1, KLED47.1, KLED48.1, KLED49.1, KLED50.1, KLED51.1, KLED52.1, KLED53.1, KLED54.1, KLED55.1, KLED56.1, KLED57.1, KLED58.1, KLED59.1, KLED60.1, KLED61.1, KLED62.1, KLED63.1, KLED64.1, KLED65.1, KLED66.1, KLED67.1, KLED68.1, KLED69.1, KLED70.1, KLED71.1, KLED72.1, KLED73.1, KLED74.1, KLED75.1, KLED76.1, KLED77.1, KLED78.1, KLED79.1, KLED80.1, KLED81.1, KLED82.1, KLED83.1, KLED84.1, KLED85.1, KLED86.1, KLED87.1, KLED88.1, MCU1.1
RST: MCU1.3, SW1.2
VCC: C2.1, C3.1, DIP1.6, DIP1.16, DIP2.16, MCU1.4
arrows_left_bottom: KD38.2, KSW38.2
arrows_left_top: KD83.2, KSW83.2
arrows_right_bottom: KD39.2, KSW39.2
arrows_right_top: KD84.2, KSW84.2
col0: DIP1.14, KSW1.1, KSW2.1, KSW3.1, KSW44.1, KSW45.1, KSW46.1
col1: DIP1.15, KSW4.1, KSW5.1, KSW6.1, KSW47.1, KSW48.1
col2: KSW7.1, KSW8.1, KSW9.1, KSW49.1, KSW50.1, KSW51.1, MCU1.10
col3: KSW10.1, KSW11.1, KSW12.1, KSW52.1, KSW53.1, KSW54.1, MCU1.9
col4: KSW13.1, KSW14.1, KSW55.1, KSW56.1, KSW57.1, MCU1.8, ROT1.1
col5: KSW15.1, KSW16.1, KSW17.1, KSW58.1, KSW59.1, KSW60.1, MCU1.7
col6: KSW18.1, KSW19.1, KSW20.1, KSW61.1, KSW62.1, KSW63.1, MCU1.6
col7: KSW21.1, KSW22.1, KSW64.1, KSW65.1, KSW66.1, MCU1.5
col8: DIP2.7, KSW23.1, KSW24.1, KSW25.1, KSW67.1, KSW68.1, KSW69.1
col9: DIP2.9, KSW26.1, KSW27.1, KSW28.1, KSW70.1, KSW71.1, KSW72.1
col10: DIP2.10, KSW29.1, KSW30.1, KSW31.1, KSW73.1, KSW74.1
col11: DIP2.11, KSW32.1, KSW33.1, KSW34.1, KSW75.1, KSW76.1, KSW77.1
col12: DIP2.12, KSW35.1, KSW36.1, KSW78.1, KSW79.1
col13: DIP2.13, KSW37.1, KSW80.1, KSW81.1, KSW82.1
col14: DIP2.14, KSW42.1, KSW83.1, KSW84.1, KSW85.1, KSW86.1, KSW87.1
col15: DIP2.15, KSW38.1, KSW39.1, KSW40.1, KSW41.1, KSW43.1, KSW88.1
encA: MCU1.11, ROT1.A
encC: MCU1.12, ROT1.C
enc_to: D2.2, ROT1.2
matrixl_index_bottom: KD55.2, KSW55.2
matrixl_index_func: KD57.2, KSW57.2
matrixl_index_home: KD13.2, KSW13.2
matrixl_index_num: KD14.2, KSW14.2
matrixl_index_top: KD56.2, KSW56.2
matrixl_inner_bottom: KD58.2, KSW58.2
matrixl_inner_func: KD60.2, KSW60.2
matrixl_inner_home: KD16.2, KSW16.2
matrixl_inner_mod: KD15.2, KSW15.2
matrixl_inner_num: KD17.2, KSW17.2
matrixl_inner_top: KD59.2, KSW59.2
matrixl_middle_bottom: KD52.2, KSW52.2
matrixl_middle_func: KD54.2, KSW54.2
matrixl_middle_home: KD11.2, KSW11.2
matrixl_middle_mod: KD10.2, KSW10.2
matrixl_middle_num: KD12.2, KSW12.2
matrixl_middle_top: KD53.2, KSW53.2
matrixl_outer_bottom: KD44.2, KSW44.2
matrixl_outer_func: KD46.2, KSW46.2
matrixl_outer_home: KD2.2, KSW2.2
matrixl_outer_mod: KD1.2, KSW1.2
matrixl_outer_num: KD3.2, KSW3.2
matrixl_outer_top: KD45.2, KSW45.2
matrixl_pinky_bottom: KD47.2, KSW47.2
matrixl_pinky_home: KD5.2, KSW5.2
matrixl_pinky_mod: KD4.2, KSW4.2
matrixl_pinky_num: KD6.2, KSW6.2
matrixl_pinky_top: KD48.2, KSW48.2
matrixl_ring_bottom: KD49.2, KSW49.2
matrixl_ring_func: KD51.2, KSW51.2
matrixl_ring_home: KD8.2, KSW8.2
matrixl_ring_mod: KD7.2, KSW7.2
matrixl_ring_num: KD9.2, KSW9.2
matrixl_ring_top: KD50.2, KSW50.2
matrixr_index_bottom: KD64.2, KSW64.2
matrixr_index_func: KD66.2, KSW66.2
matrixr_index_home: KD21.2, KSW21.2
matrixr_index_num: KD22.2, KSW22.2
matrixr_index_top: KD65.2, KSW65.2
matrixr_inner_bottom: KD61.2, KSW61.2
matrixr_inner_func: KD63.2, KSW63.2
matrixr_inner_home: KD19.2, KSW19.2
matrixr_inner_mod: KD18.2, KSW18.2
matrixr_inner_num: KD20.2, KSW20.2
matrixr_inner_top: KD62.2, KSW62.2
matrixr_middle_bottom: KD67.2, KSW67.2
matrixr_middle_func: KD69.2, KSW69.2
matrixr_middle_home: KD24.2, KSW24.2
matrixr_middle_mod: KD23.2, KSW23.2
matrixr_middle_num: KD25.2, KSW25.2
matrixr_middle_top: KD68.2, KSW68.2
matrixr_outer2_func: KD79.2, KSW79.2
matrixr_outer2_home: KD35.2, KSW35.2
matrixr_outer2_num: KD36.2, KSW36.2
matrixr_outer2_top: KD78.2, KSW78.2
matrixr_outer3_func: KD81.2, KSW81.2
matrixr_outer3_num: KD37.2, KSW37.2
matrixr_outer3_top: KD80.2, KSW80.2
matrixr_outer4_func: KD82.2, KSW82.2
matrixr_outer_bottom: KD75.2, KSW75.2
matrixr_outer_func: KD77.2, KSW77.2
matrixr_outer_home: KD33.2, KSW33.2
matrixr_outer_mod: KD32.2, KSW32.2
matrixr_outer_num: KD34.2, KSW34.2
matrixr_outer_top: KD76.2, KSW76.2
matrixr_pinky_bottom: KD73.2, KSW73.2
matrixr_pinky_home: KD30.2, KSW30.2
matrixr_pinky_mod: KD29.2, KSW29.2
matrixr_pinky_num: KD31.2, KSW31.2
matrixr_pinky_top: KD74.2, KSW74.2
matrixr_ring_bottom: KD70.2, KSW70.2
matrixr_ring_func: KD72.2, KSW72.2
matrixr_ring_home: KD27.2, KSW27.2
matrixr_ring_mod: KD26.2, KSW26.2
matrixr_ring_num: KD28.2, KSW28.2
matrixr_ring_top: KD71.2, KSW71.2
mux0: DIP1.1, DIP2.1, MCU1.17
mux1: DIP1.2, DIP2.2, MCU1.18
mux2: DIP1.3, DIP2.3, MCU1.19
mux3: DIP1.5, DIP2.6, MCU1.20
pages_left_bottom: KD40.2, KSW40.2
pages_left_top: KD85.2, KSW85.2
pages_right_bottom: KD41.2, KSW41.2
pages_right_top: KD86.2, KSW86.2
row0: D1.1, DIP1.7, KD46.1, KD51.1, KD54.1, KD57.1, KD60.1, KD63.1, KD66.1, KD69.1, KD72.1, KD77.1, KD79.1, KD81.1, KD87.1, KD88.1
row1: DIP1.9, KD3.1, KD6.1, KD9.1, KD12.1, KD14.1, KD17.1, KD20.1, KD22.1, KD25.1, KD28.1, KD31.1, KD34.1, KD36.1, KD37.1, KD42.1, KD43.1
row2: DIP1.10, KD41.1, KD45.1, KD48.1, KD50.1, KD53.1, KD56.1, KD59.1, KD62.1, KD65.1, KD68.1, KD71.1, KD74.1, KD76.1, KD78.1, KD80.1, KD86.1
row3: DIP1.11, KD2.1, KD5.1, KD8.1, KD11.1, KD13.1, KD16.1, KD19.1, KD21.1, KD24.1, KD27.1, KD30.1, KD33.1, KD35.1, KD40.1, KD82.1, KD85.1
row4: DIP1.12, KD39.1, KD44.1, KD47.1, KD49.1, KD52.1, KD55.1, KD58.1, KD61.1, KD64.1, KD67.1, KD70.1, KD73.1, KD75.1, KD84.1
row5: D2.1, DIP1.13, KD1.1, KD4.1, KD7.1, KD10.1, KD15.1, KD18.1, KD23.1, KD26.1, KD29.1, KD32.1, KD38.1, KD83.1
special_left_bottom: KD42.2, KSW42.2
special_left_top: KD87.2, KSW87.2
special_right_bottom: KD43.2, KSW43.2
special_right_top: KD88.2, KSW88.2
